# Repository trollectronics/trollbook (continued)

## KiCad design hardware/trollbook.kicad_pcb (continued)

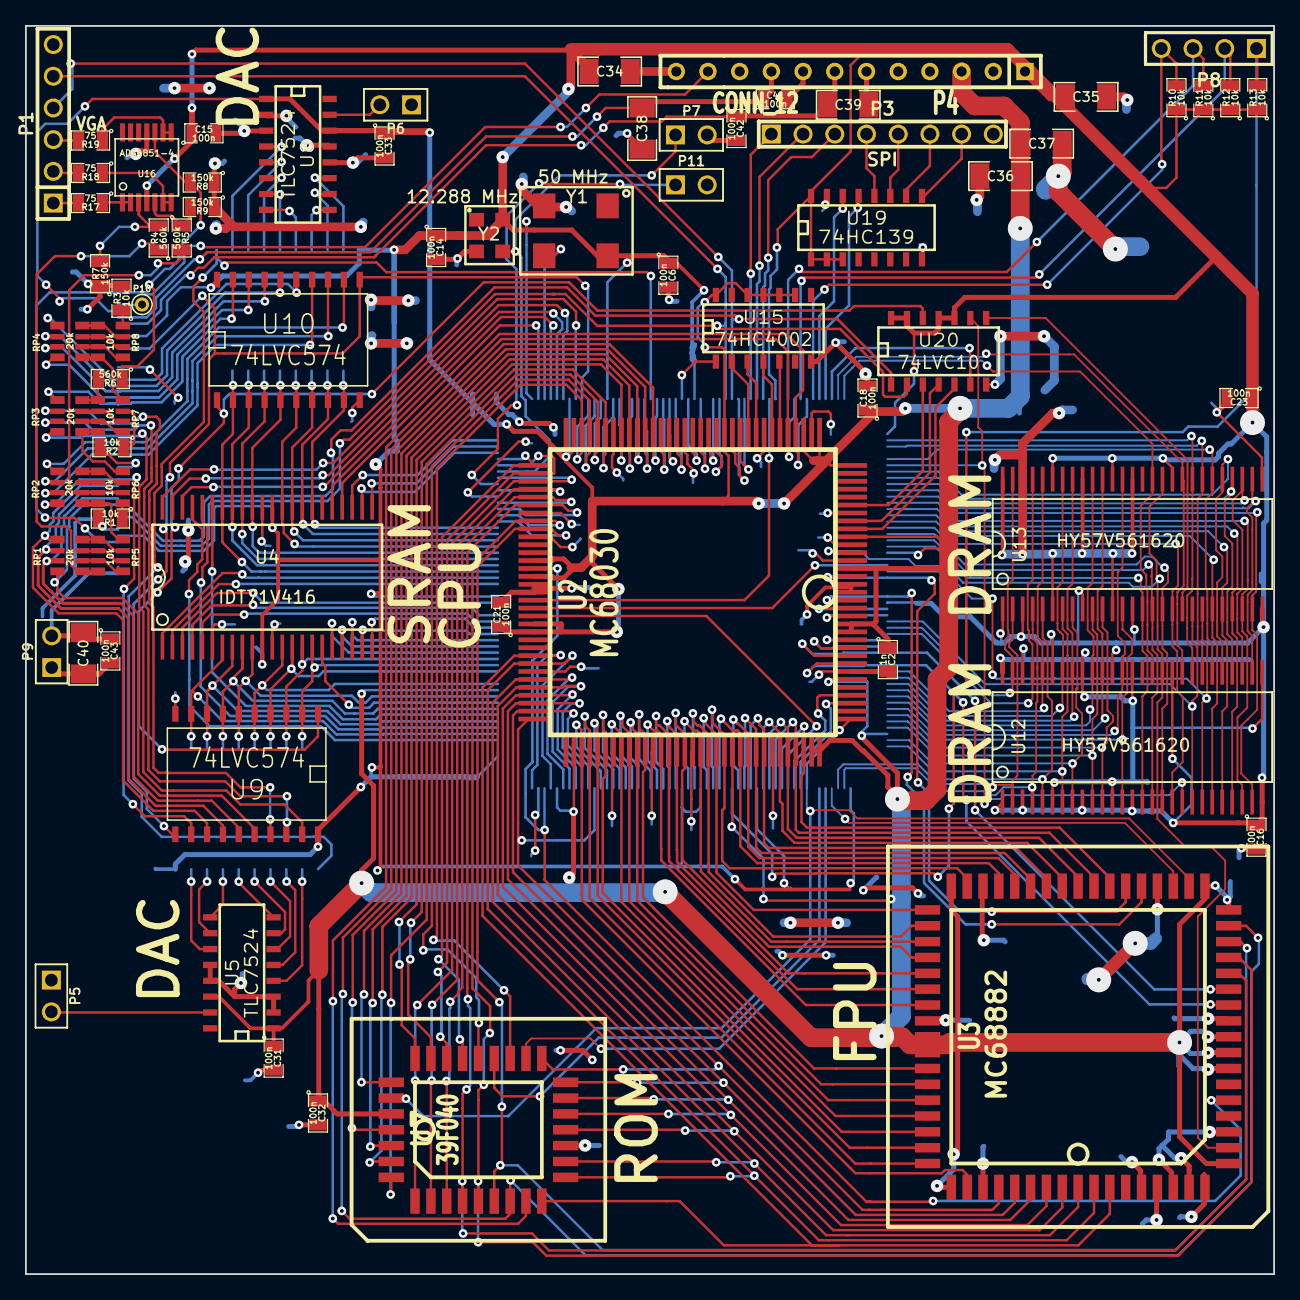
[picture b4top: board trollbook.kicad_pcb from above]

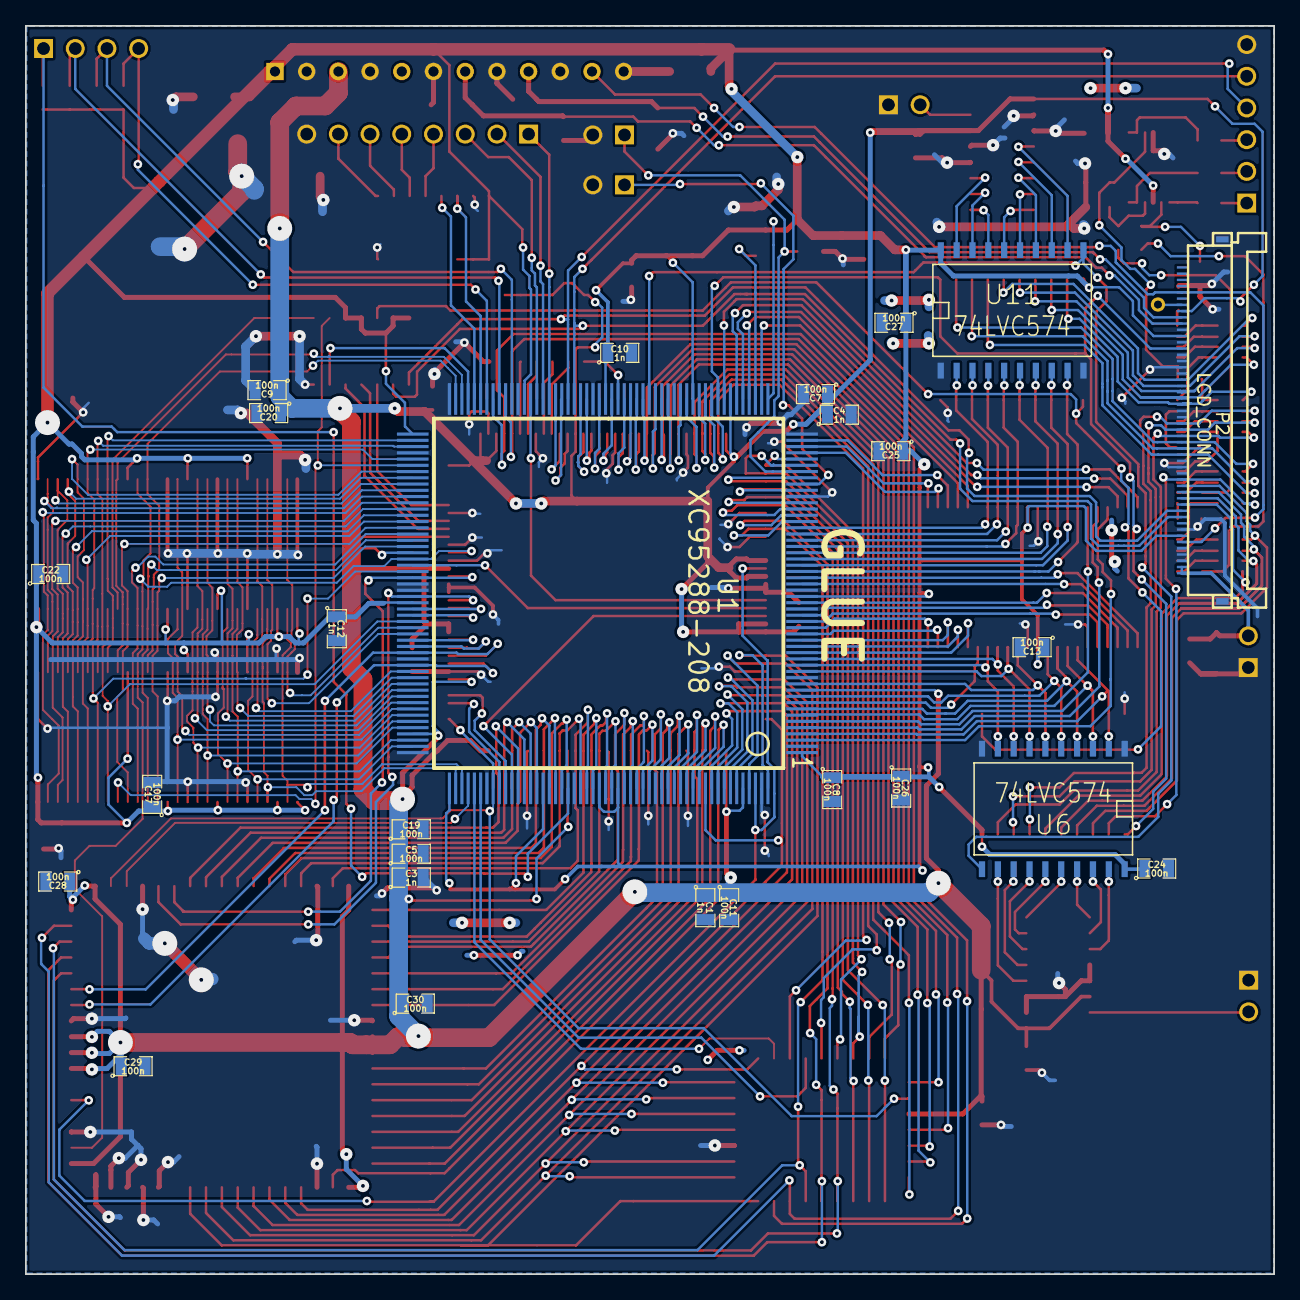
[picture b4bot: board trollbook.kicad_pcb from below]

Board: 2 copper layers, 100.0 x 100.0 mm, 97 parts (26 on the bottom side), 255 nets.

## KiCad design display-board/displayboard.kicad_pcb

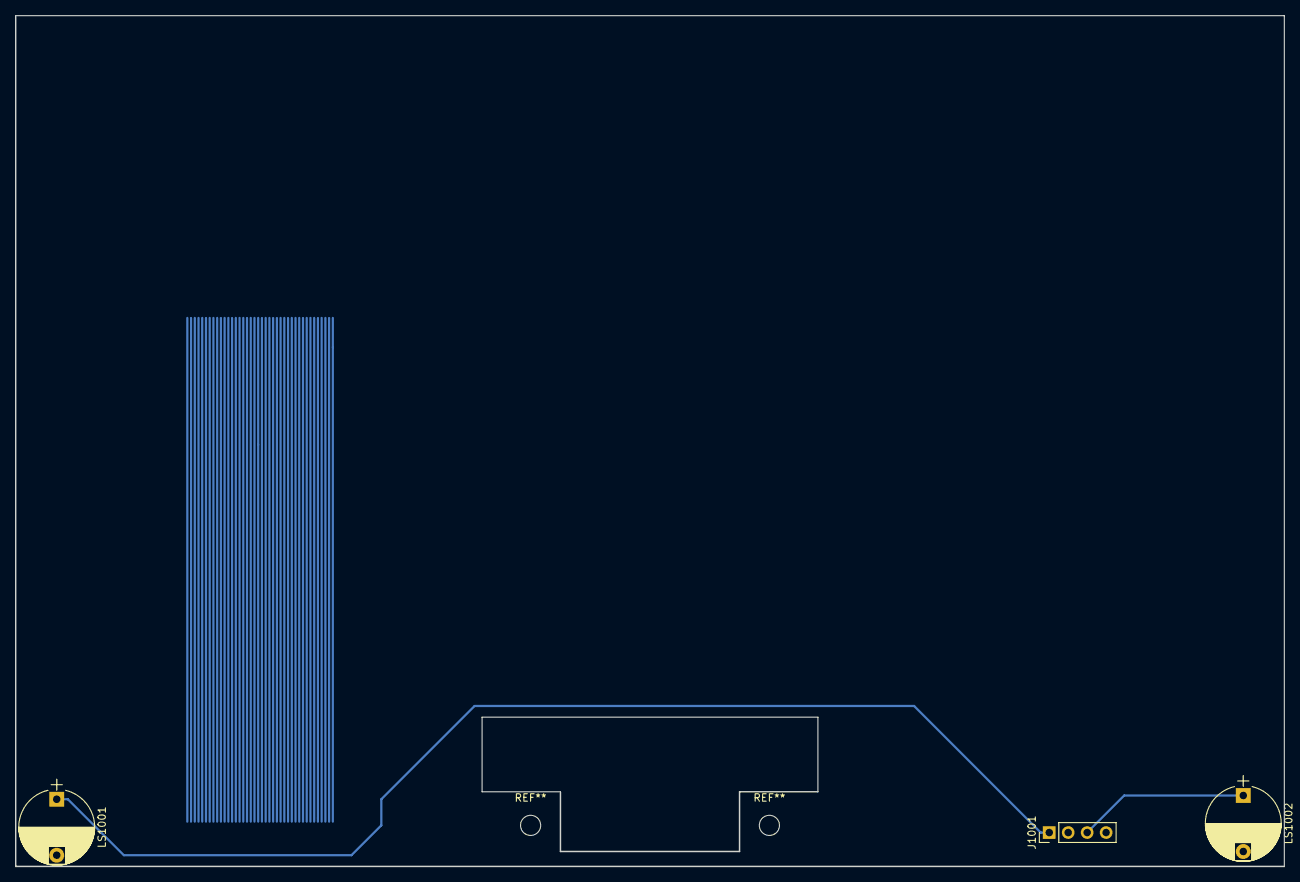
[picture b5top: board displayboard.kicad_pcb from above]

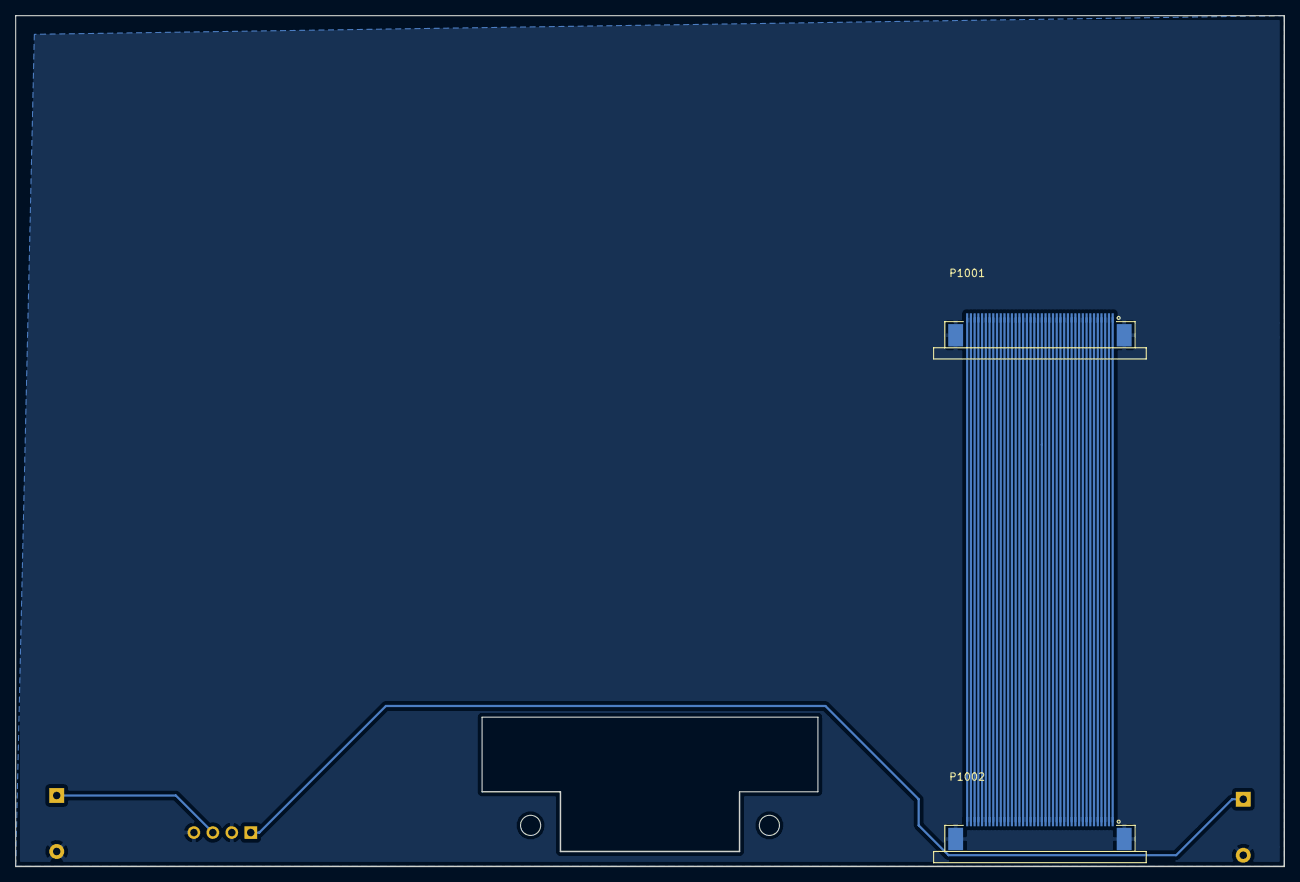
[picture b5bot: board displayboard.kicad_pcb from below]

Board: 2 copper layers, 170.0 x 114.0 mm, 5 parts (2 on the bottom side), 43 nets.

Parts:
J1001: CONN_01X04; Socket_Strip_Straight_1x04_Pitch2.54mm
LS1001: L Speaker; CP_Radial_D10.0mm_P7.50mm
LS1002: R Speaker; CP_Radial_D10.0mm_P7.50mm
P1001, P1002: ER-CON40HT-1

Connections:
GND: J1001.2, J1001.4, LS1001.2, LS1002.2, P1001.GND, P1002.GND
unnamed: J1001.1, LS1001.1
unnamed: J1001.3, LS1002.1
unnamed: P1001.1, P1002.1
unnamed: P1001.2, P1002.2
unnamed: P1001.3, P1002.3
unnamed: P1001.4, P1002.4
unnamed: P1001.5, P1002.5
unnamed: P1001.6, P1002.6
unnamed: P1001.7, P1002.7
unnamed: P1001.8, P1002.8
unnamed: P1001.9, P1002.9
unnamed: P1001.10, P1002.10
unnamed: P1001.11, P1002.11
unnamed: P1001.12, P1002.12
unnamed: P1001.13, P1002.13
unnamed: P1001.14, P1002.14
unnamed: P1001.15, P1002.15
unnamed: P1001.16, P1002.16
unnamed: P1001.17, P1002.17
unnamed: P1001.18, P1002.18
unnamed: P1001.19, P1002.19
unnamed: P1001.20, P1002.20
unnamed: P1001.21, P1002.21
unnamed: P1001.22, P1002.22
unnamed: P1001.23, P1002.23
unnamed: P1001.24, P1002.24
unnamed: P1001.25, P1002.25
unnamed: P1001.26, P1002.26
unnamed: P1001.27, P1002.27
unnamed: P1001.28, P1002.28
unnamed: P1001.29, P1002.29
unnamed: P1001.30, P1002.30
unnamed: P1001.31, P1002.31
unnamed: P1001.32, P1002.32
unnamed: P1001.33, P1002.33
unnamed: P1001.34, P1002.34
unnamed: P1001.35, P1002.35
unnamed: P1001.36, P1002.36
unnamed: P1001.37, P1002.37
unnamed: P1001.38, P1002.38
unnamed: P1001.39, P1002.39
unnamed: P1001.40, P1002.40

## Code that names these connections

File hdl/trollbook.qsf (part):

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set_global_assignment -name FLEX10K_DEVICE_IO_STANDARD LVTTL/LVCMOS
set_global_assignment -name RESERVE_ALL_UNUSED_PINS_NO_OUTPUT_GND "AS INPUT TRI-STATED"
set_global_assignment -name MISC_FILE trollbook.dpf
set_location_assignment PIN_91 -to clk33
set_location_assignment PIN_158 -to vga_vsync
set_location_assignment PIN_159 -to vga_hsync
set_location_assignment PIN_161 -to vga_b[4]
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set_location_assignment PIN_19 -to ll_ub
set_location_assignment PIN_20 -to ll_oe
set_location_assignment PIN_220 -to ll_we
set_location_assignment PIN_209 -to pwron_reset
set_location_assignment PIN_230 -to ll_ce
set_location_assignment PIN_211 -to clk12
set_location_assignment PIN_11 -to snd_clk
set_location_assignment PIN_238 -to snd_mosi
set_location_assignment PIN_236 -to snd_ss
set_location_assignment PIN_213 -to snd_sync
set_location_assignment PIN_188 -to spi_clk
set_location_assignment PIN_186 -to spi_miso
set_location_assignment PIN_190 -to spi_mosi
set_location_assignment PIN_182 -to spi_ss[2]
set_location_assignment PIN_183 -to spi_ss[1]
set_location_assignment PIN_185 -to spi_ss[0]
set_location_assignment PIN_240 -to uart_rx
set_location_assignment PIN_239 -to uart_tx
set_location_assignment PIN_26 -to cpu_clk
set_location_assignment PIN_214 -to cpu_ipl[2]
set_location_assignment PIN_208 -to cpu_ipl[1]
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
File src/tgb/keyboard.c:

#include <stdint.h>
#include <stdbool.h>
#include <string.h>
#include <avr/io.h>
#include "protocol.h"
#include "interrupt.h"

#define KBD_RESET_DEASSERT() (PORTB |= (1 << 0))
#define KBD_RESET_ASSERT() (PORTB &= ~(1 << 0))

#define KBD_CLK_ASSERT() (PORTB |= (1 << 1))
#define KBD_CLK_DEASSERT() (PORTB &= ~(1 << 1))

#define KBD_Q0 ((PINA >> 2) & 1)
#define KBD_Q1 ((PIND >> 4) & 1)
#define KBD_Q2 ((PIND >> 3) & 1)
#define KBD_Q3 ((PIND >> 1) & 1)

#define COLUMNS 17

typedef enum KeyboardState KeyboardState;
enum KeyboardState {
	KEYBOARD_STATE_RESET,
	KEYBOARD_STATE_CLK_LOW,
	KEYBOARD_STATE_CLK_HIGH,
};

struct {
	uint8_t keystate[9];
	uint8_t column;
	KeyboardState state;
	uint8_t event[8];
	uint8_t event_first;
	uint8_t event_last;
} keyboard;

uint8_t keyboard_init() {
	uint8_t row;
	DDRB |= (1 << 0); //KBD_RESET output
	DDRB |= (1 << 1); //KBD_CLK output
	DDRA &= ~(1 << 2); //KBD_Q0 input
	DDRD &= ~(1 << 4); //KBD_Q1 input
	DDRD &= ~(1 << 3); //KBD_Q2 input
	DDRD &= ~(1 << 1); //KBD_Q3 input
	KBD_CLK_DEASSERT();
	KBD_RESET_ASSERT();
	
	memset(&keyboard, 0, sizeof(keyboard));
	row = KBD_Q0 | (KBD_Q1 << 1) | (KBD_Q2 << 2) | (KBD_Q3 << 3);
	
	return row;
}

void keyboard_deinit() {
	DDRB &= ~(1 << 0); //KBD_RESET input
	DDRB &= ~(1 << 1); //KBD_CLK input
	DDRA &= ~(1 << 2); //KBD_Q0 input
	DDRD &= ~(1 << 4); //KBD_Q1 input
	DDRD &= ~(1 << 3); //KBD_Q2 input
	DDRD &= ~(1 << 1); //KBD_Q3 input
}

void keyboard_event_push(uint8_t ev) {
	uint8_t last;
	reg_status.keyboard_if = true;
	
	last = keyboard.event_last;
	keyboard.event[keyboard.event_last++] = ev;
	if(keyboard.event_last == 8)
		keyboard.event_last = 0;
	
	if(keyboard.event_last == keyboard.event_first)
		keyboard.event_last = last;
}

int16_t keyboard_event_pop() {
	uint8_t ret;
	
	if(keyboard.event_first == keyboard.event_last) {
		reg_status.keyboard_if = false;
		return -1;
	}
	
	ret = keyboard.event[keyboard.event_first++];
	if(keyboard.event_first == 8)
		keyboard.event_first = 0;
	
	if(keyboard.event_first == keyboard.event_last)
		reg_status.keyboard_if = false;
	
	return ret;
}

void keyboard_tick() {
	uint8_t row;
	uint8_t oldrow;
	uint8_t i;
	
	switch(keyboard.state) {
		case KEYBOARD_STATE_RESET:
			KBD_CLK_DEASSERT();
			KBD_RESET_DEASSERT();
			keyboard.state = KEYBOARD_STATE_CLK_LOW;
			break;
		case KEYBOARD_STATE_CLK_LOW:
			row = KBD_Q0 | (KBD_Q1 << 1) | (KBD_Q2 << 2) | (KBD_Q3 << 3);
			if(keyboard.column & 1) {
				oldrow = keyboard.keystate[keyboard.column >> 1] >> 4;
				keyboard.keystate[keyboard.column >> 1] &= 0x0F;
				keyboard.keystate[keyboard.column >> 1] |= row << 4;
			} else {
				oldrow = keyboard.keystate[keyboard.column >> 1] & 0xF;
				keyboard.keystate[keyboard.column >> 1] &= 0xF0;
				keyboard.keystate[keyboard.column >> 1] |= row;
			}
			
			for(i = 0; oldrow != row; i++) {
				if((oldrow & 1) ^ (row & 1)) {
					keyboard_event_push(((oldrow & 1) << 7) | ((keyboard.column << 2) | i));
				}
				
				oldrow >>= 1;
				row >>= 1;
			}
			
			KBD_CLK_ASSERT();
			keyboard.state = KEYBOARD_STATE_CLK_HIGH;
			break;
		case KEYBOARD_STATE_CLK_HIGH:
			if(++keyboard.column == COLUMNS)
				keyboard.column = 0;
			KBD_CLK_DEASSERT();
			keyboard.state = KEYBOARD_STATE_CLK_LOW;
			break;
	}
}

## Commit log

2014-11-14 modules for kicad: processor, cpld, co-processor, sram
2014-12-07 routed address and data lines between cpu, fpu, rom, cpld
2014-12-08 dram
2014-12-11 routed sram, dram
2014-12-12 moved sram closer to cpu
2014-12-12 lcd connector, vga dac
2014-12-16 3d models
2015-01-14 ostkaka
2015-01-15 aaaaawww yeeeaaaahhh
2015-01-15 capacitors, capacitors everywhere
2015-01-15 fixed some erc/drc violations
2015-01-15 ground plane stitching
2015-01-21 arne
2015-02-07 fixed a couple of voltage issues
2015-02-11 added rpack 3d model
2015-02-17 replaced ram footprint with the correct one
2015-02-17 lotsa 3d models :o
2015-08-25 added 040 cpu to rev2
2015-08-26 cpu footprint
2015-08-26 added fpga
2015-09-02 fixed clearance, added ram
2015-09-02 track width
2015-09-09 started connecting processor to glue
2015-09-09 added oscillator lib
2015-09-29 connectec cpu control signals, spi stuff
2015-10-23 cpu control signals, vga dac
2015-12-17 almost done
2016-01-21 now only the capacitors left
2016-02-02 added external interrupt header
2016-02-10 aligned pin headers
2016-02-21 finished all routing, only minor touch-ups left
2016-02-22 touched up silkscreen a bit
2016-02-24 minor fixes and gerbers
2016-02-29 added pcb logo
2016-03-03 gerbers
2016-03-03 corrected solder mask minimum width, now there is solder stop everywhere
2016-03-04 correct cpu name on silk screen
2016-03-23 hdl project skeleton
2016-03-23 added vga driver and top level
2016-03-23 added pin assignments for vga
2016-03-23 added all ports to hdl
2016-03-23 specify input or output for all cpu ports
2016-03-24 added all pins to pin planner
2016-03-24 added stubs for driving all signals to safe levels
2016-03-24 uart and spi stubs
2016-03-24 removed autogenerated file
2016-03-24 stupid semicolons
2016-03-24 all stubs compile
2016-03-24 added jtag chain file
2016-03-29 this does not work, tri state drivers need to be top level
2016-03-30 added proper data bus driving, reset, simple test bench
2016-03-30 corrected test bench
2016-03-30 testbench correctly testing power on reset
2016-03-31 cpu control signals seem to work
2016-03-31 replaced nop with branch to generate valid reset vectors
2016-03-31 turn of vga backlight when resetting
2016-04-01 llram - palette - vga now compiles.. probably does not work
2016-04-01 vga llram pallete timings sort of look ok now
2016-04-01 minor llram tweaks
2016-04-01 fixed vga reset sequence
2016-04-01 added palette init
2016-04-01 dunno
2016-04-02 improvements to vga
2016-04-02 got rid of some warnings
2016-04-02 aligned vga llram bus access clock to cpu bus access clock
2016-04-02 fixed vga timings
2016-04-02 driving display from llram frame buffer seems to work now o___O
2016-04-02 init all latches during reset
2016-04-03 llram access from cpu is probably glitchy as fuck but might just work..
2016-04-03 nope
2016-04-06 llram access from cpu might work now, but is very slow
2016-04-06 updated bootrom slightly
2016-04-06 should work but doesn't D:
2016-04-06 arrrgghhhh
2016-04-06 need these
2016-04-06 this is how to gitignore.
2016-04-07 Is our bus working?
2016-04-07 This is a better idea
2016-04-07 derp
2016-04-07 try render something pretty
2016-04-07 wtf, cpu can write to framebuffer o_O
2016-04-07 uart tx seems to sort of work
2016-04-08 and now rx
2016-04-08 uart now double buffered receive, bus connection
2016-04-08 uart now has something looking like a bus interface
2016-04-08 some address decoding
2016-04-09 internal cpu bus somewhat glued together with the rest
2016-04-10 created llram to bus adapter, no way this is gonna work
2016-04-10 internal cpu bus might actually work now
2016-04-10 updated bootloader code
2016-04-11 maybe this
2016-04-11 llram seems to work together with bus access
2016-04-11 reconnected uart
2016-04-11 okay, bus and vga work, serial almost works but must have delay between bytes
2016-04-11 no longer need to use two stop bits for serial
2016-04-11 aw yiss we can do 115200 baud
2016-04-11 oops, palette was flipped
2016-04-12 minor tweaks to uart tx
2016-04-12 why does hex loader not work when raw file does
2016-04-13 updated test bench for 115200 baud
2016-04-15 fixed some issues with bus and uart, still not working properly
2016-08-31 bootrom
2016-09-02 minor tweaks for simulation
2016-09-02 holy mother of donkey balls we can now read from llram o____O
2016-09-02 omfg C hexload works
2016-09-03 can load hex over serial but not jump to it.. instructions in mem seem ok though
2016-09-06 omfg shit actually works o___O
2016-09-06 hex loader now works
2016-09-06 removed stray files
2016-09-06 Achtung fulkod
2016-09-06 repaired uart tx
2016-09-07 rudimentary SPI
2016-09-07 fancier build system for stage 2 bootloader
2016-09-08 fixed failed spi merge
2016-09-08 clear bss
2016-09-08 more spi repairs
2016-09-09 vhdl code cleanup
2016-09-09 added printf to stage2 bootloader
2016-09-09 fixed reading MISO in wrong bit order
2016-09-09 fixed SPI fo rels
2016-09-09 default to 16 MHz spi freq
2016-09-09 Imported µCFAT code
2016-09-09 can now run SPI at any clock rate
2016-09-09 updated boot rom
2016-09-10 added NOP before IO read to synch pipeline
2016-09-10 ported trollcard SD card code
2016-09-10 patched together SD code and FAT code
2016-09-10 successfully talking to SD card
2016-09-10 stage 2 bootloader can now read FAT filesystems from SD card
2016-09-10 fancy menues
2016-09-11 updated stage1 loader to a leaner version
2016-09-11 first attempt at spi_loader
2016-09-14 read/write SPI ROM
2016-09-16 added hex loader to second stage bootloader, can now execute files from SD
2016-09-16 added simple bouncing square demo
2016-09-16 enable booting from SPI ROM
2016-09-19 output to uart
2016-09-20 fixed bug, printing hex with highest bit -> FF
2016-09-23 fix stage1 spi code push/pop order
2016-09-26 maybe read from sdram
2016-09-26 maybe write to sdram
2016-09-26 sdram refresh
2016-09-26 init sdram
2016-09-28 correct use of masking pins for sdram
2016-10-09 redid bus address logic for simpler chipset peripherals
2016-10-09 entity instansiation instead of component instatsiation
2016-10-09 updated testbench with new memory map
2016-10-09 updated bios code with new memory map
2016-10-09 updated stage1 with new memory map
2016-10-09 reduced memory space to meet timing requirements
2016-10-09 can now boot stage2 again if cache is disabled
2016-10-09 fixes broken cache line fetches from llram
2016-10-20 correctly handle sdram dqm for read
2016-11-02 started on peripheral board
2016-11-05 added tac switch footprint
2016-11-06 added button 3d model
2016-11-06 added keyboard scanning logic
2016-11-06 added peripheral board bus header
2016-11-06 keyboard switches and diodes placed
2016-11-08 routed keyboard
2016-11-09 some more keyboard stuff fit on this side..
2016-11-29 sdram single read/write working
2016-11-29 we can execute code from sdram!
2016-11-29 sdram hdl files
2016-11-29 stage 1 bootloader outputs character and clears screen
2016-11-29 cowboy commit: memtest
2016-11-29 cleaned up stage2 main
2016-11-29 memtestery
2016-11-30 fixed address decoding logic problems for sdram
2016-11-30 updated spi rom flasher
2016-11-30 Added new spiload, not yet hooked into anything
2016-12-01 maybe run spiload
2016-12-01 temporary keypad code
2016-12-01 temporary keyboard input
2016-12-04 added mmu code to bios
2016-12-05 bios elf loader
2016-12-05 connected elf loader to file browser
2016-12-05 run bounce demo in logical address space
2016-12-06 mmu somewhat working
2016-12-06 serial file transfer code
2016-12-06 quick and dirty client for sending files to bios over serial port
2016-12-07 run bounce in virtual address space
2017-01-10 fixed loading incorrect page sizes in elf loader
2017-01-10 fixed mmu indexing bug in bios
2017-01-16 started work on sound support
2017-01-16 added some audio circuitry
2017-01-19 added interrupt controller to hdl
2017-01-19 added back extint boot switch
2017-01-19 read correct boot switch bit
2017-01-19 updated interrupt controller
2017-02-08 added battery charger schematic
2017-02-13 added audio jack
2017-02-14 added loudspeaker
2017-02-14 audio circuitry
2017-02-14 power supply component placement
2017-02-15 audio components placement
2017-02-15 routed spi
2017-02-16 routed audio circuitry
2017-02-16 added linear 3v3 reg for keyboard micro
2017-02-16 keyboard files
2017-02-16 routed traces.
2017-02-16 routed misc signals to micro
2017-02-18 misc traces, headphone jack 3d
2017-02-18 sd card 3d model
2017-02-18 added expansion port 3d model
2017-02-19 fixed various drc errors
2017-02-19 minor fixes
2017-02-19 connected 3v3 net
2017-02-19 psp nub 3d model
2017-02-19 added 3d models of the whole boards to cad directory
2017-02-20 added speaker and battery connectors
2017-02-20 peripheral board all done o____O
2017-02-21 touched up silkscreen
2017-02-21 updated peripheral board 3d model
2017-04-05 mouse connected to adc pins
2017-04-05 removed old gerbers
2017-04-05 moved power supply capacitor to accomodate larger battery
2017-04-05 updated gerber
2017-04-06 added display board
2017-04-21 keyboard controller basic power management code
2017-04-22 added spi functions
2017-04-25 power code running from interrupts
2017-04-25 keyboard can interrupt
2017-04-25 fixed faulty schematic in battery balancer
2017-04-25 added keyboard testing code
2017-04-25 stage2 talking to keyboard
2017-04-26 can now use keyboard to navigate menus
2017-04-26 reset spi clockdiv
2017-04-26 keyboard controller circular buffer
2017-05-02 proper keyboard in place and working
2017-05-02 added delay to keyboard code
2017-05-03 updated reset timings
2017-05-04 muon's ui ported to trollbook bios
2017-05-04 cleaned up build system for trollbook bios
2017-05-04 bitmap drawing and new font
2017-05-05 updated video timings for external vga
2017-05-05 added hardware cursor
2017-05-05 added sound hardware to hdl
2017-05-06 sound seems to be working, but without interrupts
2017-05-06 sound interrupt
2017-05-06 working wave file playback
2017-05-06 and stop audio hardware when done
2017-05-06 added progress indication when loading wave file
2017-05-07 added video backlight pwm
2017-05-07 added low-res video mode
2017-05-07 fixes to low-res mode
2017-05-07 split common source files out to libraries
2017-05-07 moved stuff to peripheral library
2017-05-08 minor fixes to peripheral board
2017-05-08 moved more code to libraries
2017-05-08 more audio circuit fixes
2017-05-15 plays mods~ish?
2017-05-17 fixed sdram timing issues by disabling burst writes
2017-06-30 re-added timer hardware
2018-01-12 updated kicad schematics to kicad v5
2018-01-12 added mouse to keyboard controller
2018-01-13 added input handling to muil
2018-01-14 modplayer ui
2018-01-14 moved audio buffer out of frame buffer
2018-01-14 can now play another mod when first is done
2018-01-14 don't put audio buffer in bios info area
2018-01-14 do not change the mouse cursor
2018-01-14 play audio using interrupts
2018-01-15 fancier mod player!
2018-01-19 repository cleanup
2018-01-19 use relative path for pcb 3d models
2018-01-21 removed crud from bios
2018-01-21 move mmu page table area
2018-01-21 added debug mode
2018-01-28 tgb -> kbd
2018-04-13 microcontroller mouse movement now working
2018-04-15 added extra cycles in hopes that it would make sdram access more reliable..
2018-04-22 changed timers to common prescaler + 16 bit to save space
2018-04-22 more mouse dead zone
2018-04-22 fixed glitchy mouse cursor when at the end of the screen
2018-04-22 timers and interrupt priority works
2018-07-21 added support for digitizer
2018-07-21 better delay function
2018-07-21 added tsko repo
2018-07-21 ungzip
2018-07-21 load some images
2018-07-21 fixed ungzip
2018-07-21 intro
2018-07-24 finally found my lz4 inflater
2021-12-11 vga hdl implement palette writes
2023-07-08 add uart interrupt
